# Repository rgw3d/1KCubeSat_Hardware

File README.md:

# 1KCubeSat_Hardware

Hardware design files for my $1000 cubesat.

Schematics & Layouts are done using KiCad V5.1+

## ½ CubeSat

My progress so far, what I'm calling the ½ Cubesat. The [avionics board](avionics_board) is stacked on the [eps board](eps_board)

## Radio Board

See [my fork of the OpenLST repo](https://github.com/rgw3d/openlst-hw/tree/1kcubesat-updates) for more information!

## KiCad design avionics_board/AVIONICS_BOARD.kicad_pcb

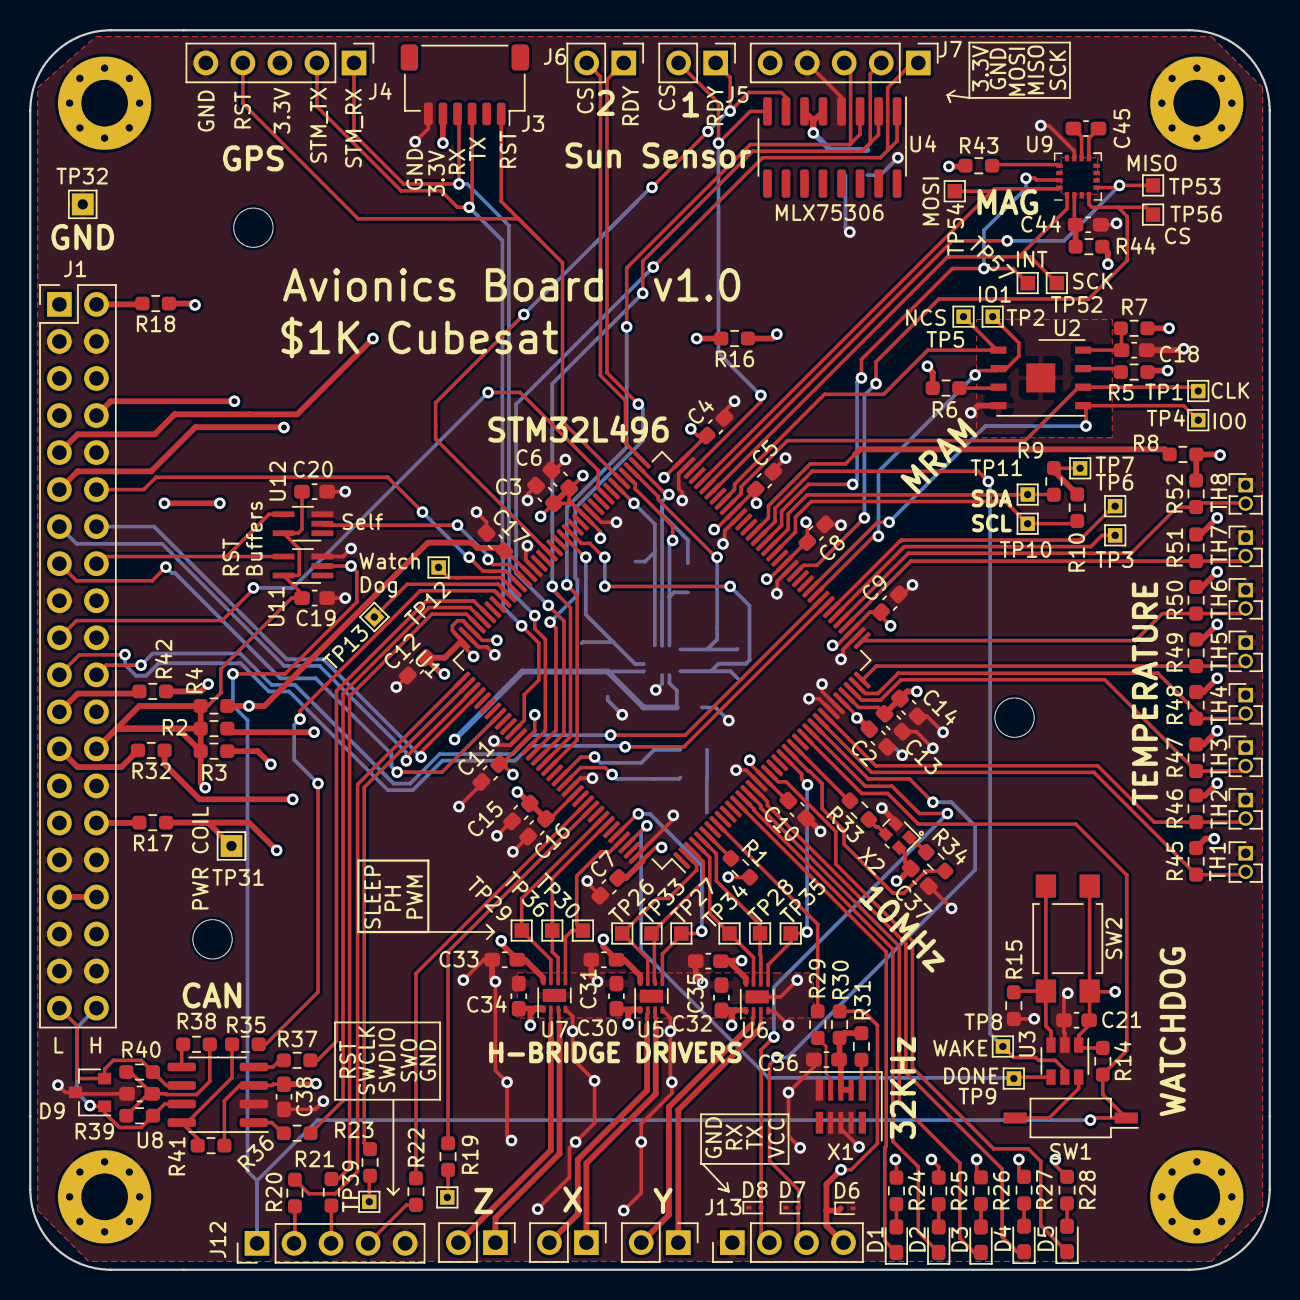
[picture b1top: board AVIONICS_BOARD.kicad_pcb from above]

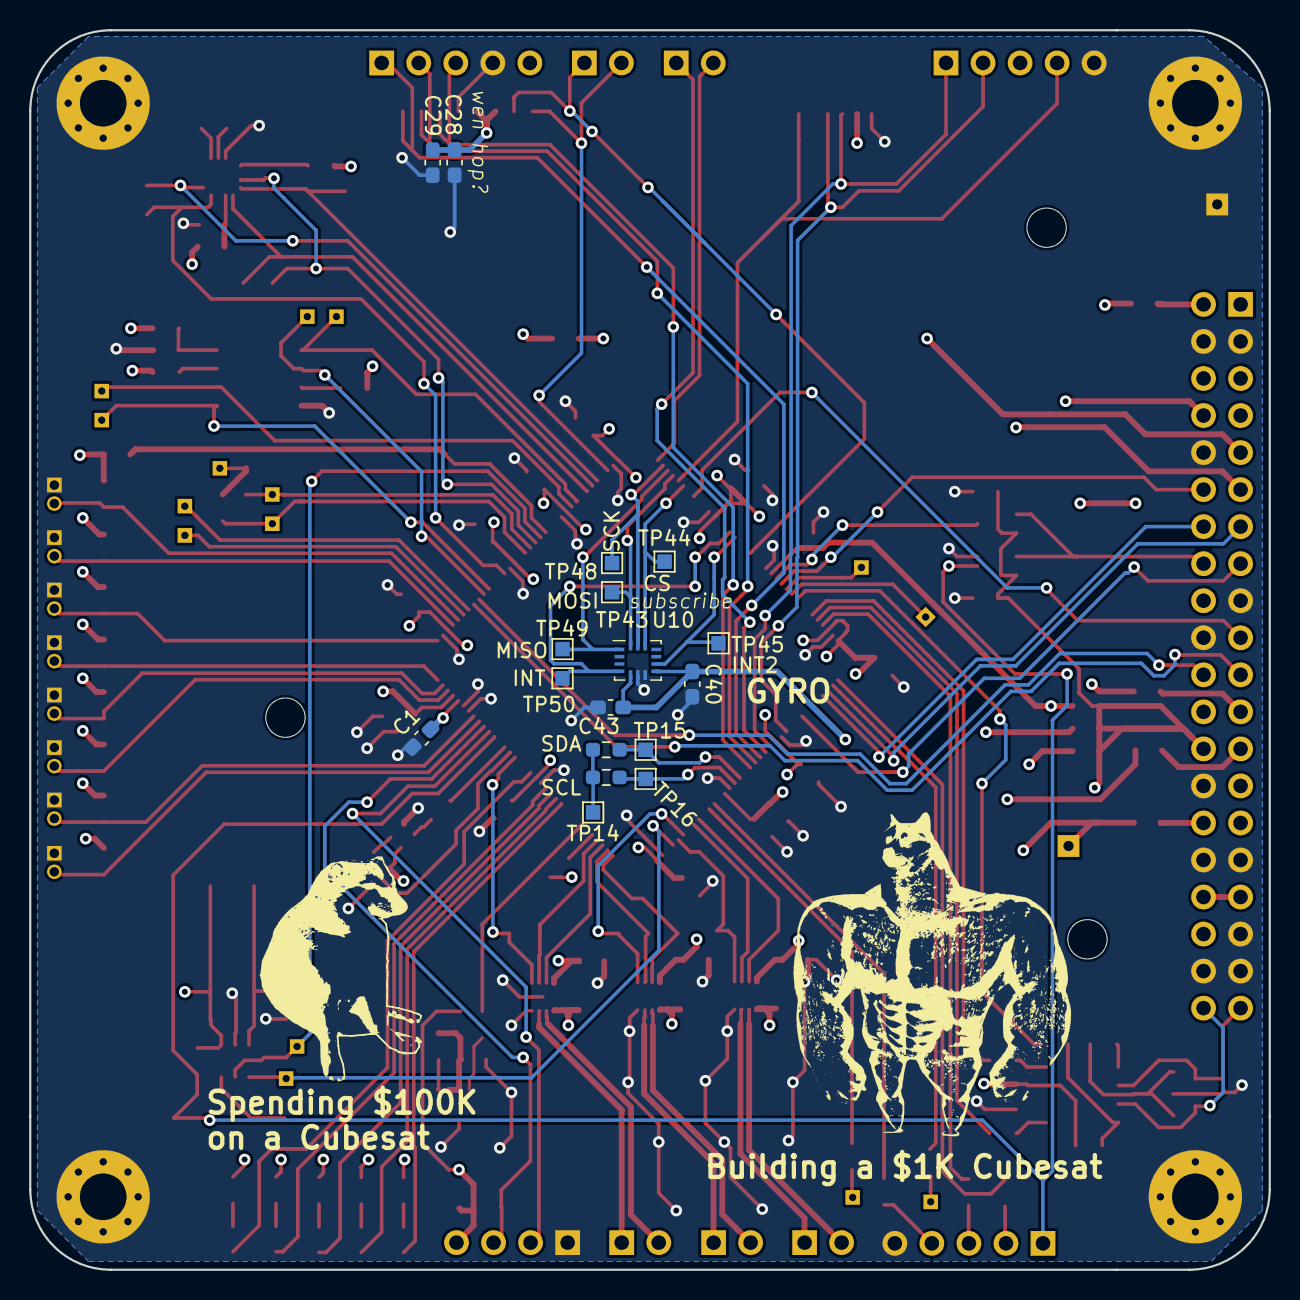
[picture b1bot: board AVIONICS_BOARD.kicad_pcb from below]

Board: 4 copper layers, 85.0 x 85.0 mm, 179 parts (17 on the bottom side), 143 nets.

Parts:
C1, C2, C13: 0.01uF; C_0603_1608Metric_Pad1.08x0.95mm_HandSolder
C3, C15: 4.7uF; C_0603_1608Metric_Pad1.08x0.95mm_HandSolder
C4, C5, C6, C7, C8, C9, C10, C11, C12, C16, C17, C18, C19, C20, C21, C29, C30, C31, C32, C33, C34, C35, C36, C37, C38, C40, C43: 0.1uF; C_0603_1608Metric_Pad1.08x0.95mm_HandSolder
C14, C28, C44: 1uF; C_0603_1608Metric_Pad1.08x0.95mm_HandSolder
C39: 4.7nF; C_0603_1608Metric_Pad1.08x0.95mm_HandSolder
C45: 10uF; C_0603_1608Metric_Pad1.08x0.95mm_HandSolder
D1: LED_SMD_RED; LED_0603_1608Metric_Pad1.05x0.95mm_HandSolder
D2: LED_SMD_GREEN; LED_0603_1608Metric_Pad1.05x0.95mm_HandSolder
D3, D4, D5: LED_SMD_YELLOW; LED_0603_1608Metric_Pad1.05x0.95mm_HandSolder
D6, D7, D8: ESD9B5.0ST5G; D_SOD-923
D9: NUP2105L; SOT-23
H1, H2, H3, H4: MountingHole_Pad; MountingHole_3.2mm_M3_Pad_Via
H5, H6, H7: MountingHole; MountingHole_2.7mm
J1: Conn_02x20_Odd_Even; PinHeader_2x20_P2.54mm_Vertical
J3: JST socket 6-pin 1mm pitch JST SH SM06B-SRSS-TB; JST_SH_SM06B-SRSS-TB_1x06-1MP_P1.00mm_Horizontal
J4, J7, J12: Conn_01x05; PinHeader_1x05_P2.54mm_Vertical
J5, J6, J9, J10, J11: Conn_01x02; PinHeader_1x02_P2.54mm_Vertical
J13: Conn_01x04_Male; PinHeader_1x04_P2.54mm_Vertical
R1, R8, R16, R17, R18, R29, R30, R31, R32, R33, R34, R35, R36, R37, R38, R42, R43, R44: 0; R_0603_1608Metric_Pad0.98x0.95mm_HandSolder
R2, R3, R4, R7: 10m; R_0603_1608Metric_Pad0.98x0.95mm_HandSolder
R5, R6, R14, R41: 100K; R_0603_1608Metric_Pad0.98x0.95mm_HandSolder
R9, R10, R11, R12: DNP; R_0603_1608Metric_Pad0.98x0.95mm_HandSolder
R15: 8.85K; R_0603_1608Metric_Pad0.98x0.95mm_HandSolder
R19, R20, R21, R22, R23: 49.9; R_0603_1608Metric_Pad0.98x0.95mm_HandSolder
R24, R25, R26, R27, R28: 330; R_0603_1608Metric_Pad0.98x0.95mm_HandSolder
R39, R40: 60.4; R_0603_1608Metric_Pad0.98x0.95mm_HandSolder
R45, R46, R47, R48, R49, R50, R51, R52: 47K; R_0603_1608Metric_Pad0.98x0.95mm_HandSolder
SW1: SW_DIP_x01; SW_DIP_SPSTx01_Slide_Copal_CHS-01B_W7.62mm_P1.27mm
SW2: SW_Push; SW_SPST_TL3305A
TH1, TH2, TH3, TH4, TH5, TH6, TH7, TH8: Thermistor_NTC; PinHeader_1x02_P1.27mm_Vertical
TP1, TP2, TP3, TP4, TP5, TP6, TP8, TP9: TP_smt_1x1; TestPoint_THTPad_1.0x1.0mm_Drill0.5mm
TP7, TP10, TP11, TP12, TP13: TP_tht_1x1; TestPoint_THTPad_1.0x1.0mm_Drill0.5mm
TP14, TP15, TP16, TP26, TP27, TP28, TP29, TP30, TP33, TP34, TP35, TP36, TP43, TP44, TP45, TP48, TP49, TP50, TP52, TP53, TP54, TP56, TP57: TP_smt_1x1; TestPoint_Pad_1.0x1.0mm
TP31, TP32: TP_1.5x1.5; TestPoint_THTPad_1.5x1.5mm_Drill0.7mm
TP37, TP39: TP_1.5x1.5; TestPoint_THTPad_1.0x1.0mm_Drill0.5mm
U1: STM32L496ZGTx; LQFP-144_20x20mm_P0.5mm
U2: MR25H10; DFN-8-1EP_6x5mm_P1.27mm_EP2x2mm
U3: TPL5010; SOT-23-6
U4: MLX75306; SOIC-16_3.9x9.9mm_P1.27mm
U5, U6, U7: DRV8838; WSON-8-1EP_2x2mm_P0.5mm_EP0.9x1.6mm
U8: SN65HVD230; SOIC-8_3.9x4.9mm_P1.27mm
U9: MMC5983MA; LGA-16_3x3mm_P0.5mm
U10: BMG250; Bosch_LGA-14_3x2.5mm_P0.5mm
U11, U12: 74LVC1G07; SOT-353_SC-70-5_Handsoldering
X1: TG-3541CE; Oscillator_SMD_SeikoEpson_TG3541CE-10Pin_3.2x2.5mm_HandSold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
X2: ECS-TXO-2016; Oscillator_SMD_ECS_TXO-2016-xx-xxx-4Pin_2.0x1.6mm

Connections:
/STM32L4/3.3V_ACS_LOGIC: J1.2, R18.2
/STM32L4/3.3V_CAN: C38.1, J1.5, R41.1, U8.3
/STM32L4/3.3V_CLK: J1.25, R32.2
/STM32L4/3.3V_GPS: J1.24, J3.5, J4.3
/STM32L4/3.3V_GYRO: J1.23, R42.2
/STM32L4/3.3V_MAG: J1.8, R43.2, R44.2
/STM32L4/3.3V_MRAM: J1.11, R5.1, R6.1, R7.2
/STM32L4/3.3V_SUN_SENSOR: J1.9, R16.2
/STM32L4/5V_ACS_COIL: J1.30, R17.2
/STM32L4/10MHZ_OE: R34.2, U1.22
/STM32L4/ACS/PWR_COIL: C30.1, C32.1, C34.1, R17.1, TP31.1, U5.1, U6.1, U7.1
/STM32L4/ACS/PWR_LOGIC: C31.1, C33.1, C35.1, R18.1, U5.8, U6.8, U7.8
/STM32L4/ACS_X_PH: TP33.1, U1.3, U5.6
/STM32L4/ACS_X_SLEEP: TP26.1, U1.2, U5.7
/STM32L4/ACS_Y_PH: TP28.1, U1.5, U6.6
/STM32L4/ACS_Y_SLEEP: TP34.1, U1.4, U6.7
/STM32L4/ACS_Z_PH: TP36.1, U1.137, U7.6
/STM32L4/ACS_Z_SLEEP: TP29.1, U1.136, U7.7
/STM32L4/ADC1_IN3: R45.1, TH1.2, U1.28
/STM32L4/ADC1_IN4: R46.1, TH2.2, U1.29
/STM32L4/ADC1_IN5: R47.1, TH3.2, U1.34
/STM32L4/ADC1_IN6: R48.1, TH4.2, U1.35
/STM32L4/ADC1_IN7: R49.1, TH5.2, U1.36
/STM32L4/ADC1_IN8: R50.1, TH6.2, U1.37
/STM32L4/ADC1_IN9: R51.1, TH7.2, U1.40
/STM32L4/ADC1_IN10: R52.1, TH8.2, U1.41
/STM32L4/ADC1_IN11: TP3.1, U1.42
/STM32L4/ADC1_IN12: TP6.1, U1.43
/STM32L4/AVI_RST: J1.16, U11.4, U12.4
/STM32L4/CAN1_RX: R37.2, U1.103
/STM32L4/CAN1_TX: R36.2, U1.104
/STM32L4/CAN_RS: R35.2, U1.100
/STM32L4/CAN_TRANSCEIVER/CANH: D9.1, J1.40, R39.1, U8.7
/STM32L4/CAN_TRANSCEIVER/CANL: D9.2, J1.39, R40.2, U8.6
/STM32L4/CAN_TRANSCEIVER/Vref: R38.2, U8.5
/STM32L4/EPS_RST: J1.12, U1.97
/STM32L4/GPS_RESET: J3.1, J4.4, U1.77
/STM32L4/GYRO_CS: TP44.1, U1.78, U10.12
/STM32L4/GYRO_INT_1: TP50.1, U1.87, U10.4
/STM32L4/GYRO_INT_2: TP45.1, U1.88, U10.9
/STM32L4/I2C1_SCL: R11.2, TP16.1, U1.129
/STM32L4/I2C1_SDA: R12.2, TP15.1, U1.128
/STM32L4/I2C4_SCL: R10.2, TP10.1, U1.54
/STM32L4/I2C4_SDA: R9.2, TP11.1, U1.55
/STM32L4/JTCK_SWCLK: R20.1, U1.109
/STM32L4/JTDI: R23.1, U1.110
/STM32L4/JTDO_TRACESWO: R22.1, U1.133
/STM32L4/JTMS_SWDIO: R21.1, U1.105
/STM32L4/LED_1: D1.1, U1.12
/STM32L4/LED_2: D2.1, U1.13
/STM32L4/LED_3: D3.1, U1.14
/STM32L4/LED_4: D4.1, U1.15
/STM32L4/LED_5: D5.1, U1.18
/STM32L4/LPUART1_RX: D8.2, J13.2, U1.26
/STM32L4/LPUART1_TX: D7.2, J13.3, U1.27
/STM32L4/MAG_CS: TP56.1, U1.50, U9.4
/STM32L4/MAG_INT: TP57.1, U1.56, U9.15
/STM32L4/MANUAL_RST: U1.96, U12.2
/STM32L4/NJRST: R19.1, U1.134
/STM32L4/OSC32_TCXO/OE: R31.1, X1.1
/STM32L4/QUADSPI_BK1_IO0: TP4.1, U1.47, U2.5
/STM32L4/QUADSPI_BK1_IO1: TP2.1, U1.46, U2.2
/STM32L4/QUADSPI_BK1_NCS: TP5.1, U1.64, U2.1
/STM32L4/QUADSPI_CLK: TP1.1, U1.63, U2.6
/STM32L4/RCC_OSC32_IN: R29.2, U1.8
/STM32L4/RCC_OSC_IN: R33.2, U1.23
/STM32L4/RST: J12.1, R14.2, SW1.1, U1.25, U11.2
/STM32L4/SPI1_MISO: TP53.1, U1.67, U9.5
/STM32L4/SPI1_MOSI: TP54.1, U1.68, U9.16
/STM32L4/SPI1_SCK: TP52.1, U1.66, U9.1
/STM32L4/SPI2_MISO: TP49.1, U1.75, U10.1
/STM32L4/SPI2_MOSI: TP43.1, U1.76, U10.14
/STM32L4/SPI2_SCK: TP48.1, U1.74, U10.13
/STM32L4/SPI3_MISO: J7.2, U1.125, U4.2
/STM32L4/SPI3_MOSI: J7.3, U1.126, U4.3
/STM32L4/SPI3_SCK: J7.1, U1.124, U4.1
/STM32L4/SUN_CS_1: J5.2, U1.70, U4.8
/STM32L4/SUN_CS_2: J6.2, U1.73
/STM32L4/SUN_FRAME_RDY_1: J5.1, U1.91, U4.7
/STM32L4/SUN_FRAME_RDY_2: J6.1, U1.123
/STM32L4/Sheet639EBCAF/5V0_2: J1.33, J1.34
/STM32L4/TEMPERATURE_ADC/INTRNL_VDD: R8.1, R45.2, R46.2, R47.2, R48.2, R49.2, R50.2, R51.2, R52.2
/STM32L4/TEMP_PWR: R8.2, U1.58
/STM32L4/TIM15_CH1: TP35.1, U1.21, U6.5
/STM32L4/TIM16_CH1: TP27.1, U1.139, U5.5
/STM32L4/TIM17_CH1: TP30.1, U1.140, U7.5
/STM32L4/UART4_RX: J1.14, U1.112
/STM32L4/UART4_TX: J1.13, U1.111
/STM32L4/USART2_RX: J3.4, J4.1, U1.122
/STM32L4/USART2_TX: J3.3, J4.2, U1.119
/STM32L4/USART3_CTS: J1.19, U1.80
/STM32L4/USART3_RTS: J1.15, U1.116
/STM32L4/USART3_RX: J1.22, U1.45
/STM32L4/USART3_TX: J1.21, U1.44
/STM32L4/WATCHDOG_DONE: TP9.1, U1.141, U3.4
/STM32L4/WATCHDOG_WAKE: TP8.1, U1.57, U3.5
GND: C1.1, C2.1, C3.1, C4.2, C5.2, C6.2, C7.2, C8.2, C9.2, C10.2, C11.1, C12.1, C13.2, C14.2, C15.1, C16.1, C17.1, C18.2, C19.1, C20.1, C21.2, C28.2, C29.2, C30.2, C31.2, C32.2, C33.2, C34.2, C35.2, C36.2, C37.2, C38.2, C39.2, C40.2, C43.2, C44.2, D6.2, D7.1, D8.1, D9.3, H1.1, H2.1, H3.1, H4.1, J1.3, J1.4, J1.10, J1.17, J1.20, J1.28, J1.31, J1.32, J1.35, J1.37, J1.38, J3.6, J4.5, J7.4, J12.5, J13.1, R15.2, TH1.1, TH2.1, TH3.1, TH4.1, TH5.1, TH6.1, TH7.1, TH8.1, TP32.1, U1.16, U1.30, U1.31, U1.38, U1.51, U1.61, U1.71, U1.83, U1.94, U1.107, U1.120, U1.130, U1.143, U2.4, U2.9, U3.2, U4.4, U5.4, U5.9, U6.4, U6.9, U7.4, U7.9, U8.2, U9.11, U10.6, U10.7, U11.3, U12.3, X1.5, X1.7, X1.8, X1.9, X2.2
unnamed: C1.2, C2.2, U1.32
unnamed: C3.2, C4.1, C5.1, C6.1, C7.1, C8.1, C9.1, C10.1, C11.2, C12.2, R1.2, R2.2, U1.17, U1.39, U1.52, U1.62, U1.72, U1.84, U1.106, U1.108, U1.121, U1.144
unnamed: C13.1, C14.1, R3.2, U1.33
unnamed: C15.2, C16.2, C17.2, R4.2, U1.95, U1.131
unnamed: C18.1, R7.1, U2.8
unnamed: C28.1, C29.1, J7.5, R16.1, U4.5, U4.6
unnamed: C36.1, R30.1, R31.2, X1.2, X1.3
unnamed: C37.1, R32.1, X2.4
unnamed: C39.1, R38.1, R39.2, R40.1
unnamed: C40.1, C43.1, R42.1, U10.5, U10.8
unnamed: C44.1, R44.1, U9.2
unnamed: C45.1, U9.9
unnamed: C45.2, U9.10
unnamed: D1.2, R24.2
unnamed: D2.2, R25.2
unnamed: D3.2, R26.2
unnamed: D4.2, R27.2
unnamed: D5.2, R28.2
unnamed: J9.1, U5.3
unnamed: J9.2, U5.2
unnamed: J10.1, U6.3
unnamed: J10.2, U6.2
unnamed: J11.1, U7.3
unnamed: J11.2, U7.2
unnamed: J12.2, R20.2
unnamed: J12.3, R21.2
unnamed: J12.4, R22.2
unnamed: R1.1, U1.6
unnamed: R5.2, U2.7
unnamed: R6.2, U2.3
unnamed: R9.1, R10.1, TP7.1
unnamed: R11.1, R12.1, TP14.1
unnamed: R15.1, SW2.2, U3.3
unnamed: R19.2, TP37.1
unnamed: R23.2, TP39.1
unnamed: R29.1, X1.4
unnamed: R33.1, X2.3
unnamed: R34.1, X2.1
unnamed: R35.1, R41.2, U8.8
unnamed: R36.1, U8.1
unnamed: R37.1, U8.4
unnamed: R43.1, U9.13
unnamed: SW1.2, U3.6
unnamed: TP12.1, U1.98
unnamed: TP13.1, U1.99
VCC: C19.2, C20.2, C21.1, D6.1, J1.26, J13.4, R2.1, R3.1, R4.1, R14.1, R24.1, R25.1, R26.1, R27.1, R28.1, R30.2, SW2.1, U3.1, U11.5, U12.5

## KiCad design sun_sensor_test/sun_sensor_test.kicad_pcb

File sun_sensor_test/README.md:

# Sun Sensor Test

Testing out a potential sun sensor using the K857PE 4-Quadrent Photodiode. See the [pdf](https://raw.githubusercontent.com/rgw3d/1KCubeSat_Hardware/master/sun_sensor_test/sun_sensor_test.pdf) for more information.

See [my video on this board](https://www.youtube.com/watch?v=8ttuiI6RIH0) for more information.

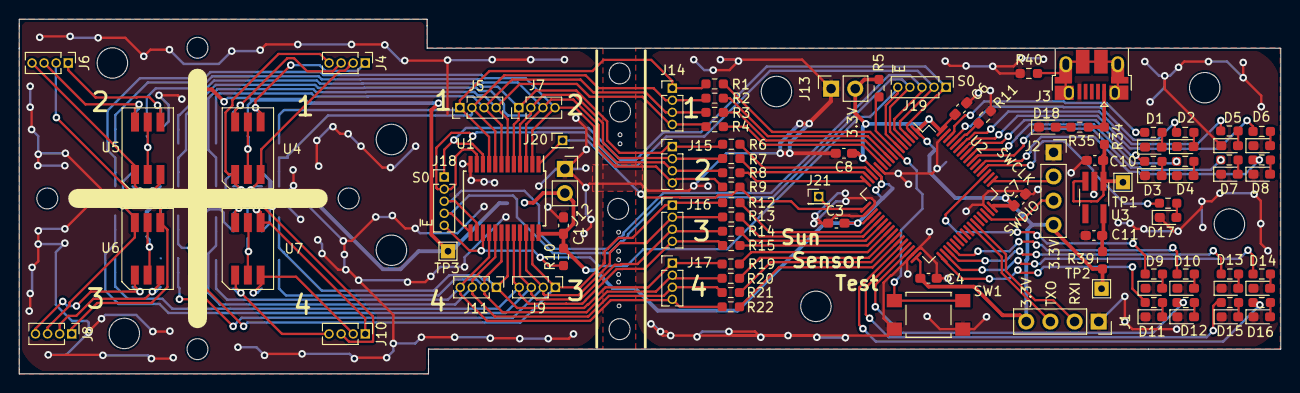
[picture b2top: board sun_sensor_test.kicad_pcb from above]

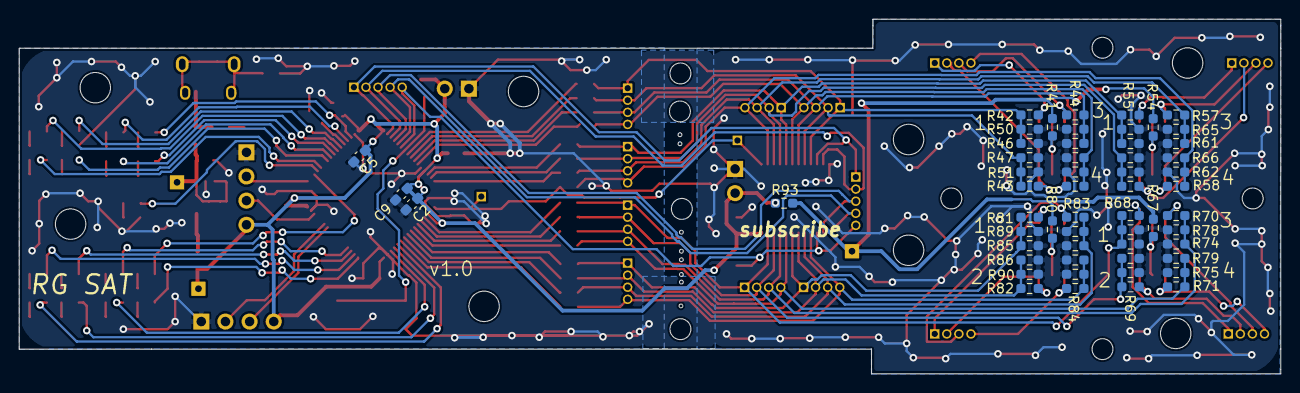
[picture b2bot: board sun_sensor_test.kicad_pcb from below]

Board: 2 copper layers, 132.7 x 37.3 mm, 178 parts (56 on the bottom side), 105 nets.

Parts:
C1, C2, C3, C4, C5, C6, C7: 0.1uF; C_0603_1608Metric_Pad1.08x0.95mm_HandSolder
C8, C9: 1uF; C_0603_1608Metric_Pad1.08x0.95mm_HandSolder
C10, C11: 4.7uF; C_0603_1608Metric_Pad1.08x0.95mm_HandSolder
D1, D2, D3, D4, D5, D6, D7, D8, D9, D10, D11, D12, D13, D14, D15, D16, D17, D18: RED; LED_0603_1608Metric_Pad1.05x0.95mm_HandSolder
H1, H2, H3, H4, H5, H6, H7, H8: M2 Screw; MountingHole_2.2mm_M2_ISO7380
H9, H10, H11, H12, H13, H14, H15, H16: M3 Screw; MountingHole_3.2mm_M3
H17, H18, H19, H20, H21, H23, H24, H25: mousebite
J1, J2: 2.54mm; PinSocket_1x04_P2.54mm_Vertical
J3: USB_B_Micro; USB_Micro-B_Amphenol_10103594-0001LF_Horizontal
J4, J5, J6, J7, J8, J9, J10, J11, J14, J15, J16, J17: Conn_01x04_Female; PinHeader_1x04_P1.27mm_Vertical
J12, J13: Conn_01x02; PinSocket_1x02_P2.54mm_Vertical
J18, J19: Conn_01x05_Female; PinHeader_1x05_P1.27mm_Vertical
J20, J21: 1.27mm; PinHeader_1x01_P1.27mm_Vertical
R1, R2, R3, R4, R6, R7, R8, R9, R12, R13, R14, R15, R19, R20, R21, R22, R40, R46, R47, R48, R49, R50, R51, R52, R53, R59, R60, R61, R62, R63, R64, R65, R66, R72, R73, R74, R75, R76, R77, R78, R79, R85, R86, R87, R88, R89, R90, R91, R92: DNP; R_0603_1608Metric_Pad0.98x0.95mm_HandSolder
R5, R11: 10K; R_0603_1608Metric_Pad0.98x0.95mm_HandSolder
R10: 100K; R_0603_1608Metric_Pad0.98x0.95mm_HandSolder
R16, R17, R18, R23, R24, R25, R26, R27, R28, R29, R30, R31, R32, R33, R36, R37, R38: 680; R_0603_1608Metric_Pad0.98x0.95mm_HandSolder
R34, R39, R41, R42, R43, R44, R45, R54, R55, R56, R57, R58, R67, R68, R69, R70, R71, R80, R81, R82, R83, R84, R93: 0; R_0603_1608Metric_Pad0.98x0.95mm_HandSolder
R35: 330; R_0603_1608Metric_Pad0.98x0.95mm_HandSolder
SW1: SW_Push; SW_SPST_TL3305A
TP1, TP2, TP3: TP_1.5x1.5; TestPoint_THTPad_1.5x1.5mm_Drill0.7mm
U1: CD74HC4067SM; SSOP-24_5.3x8.2mm_P0.65mm
U2: STM32L051R8Tx; LQFP-64_10x10mm_P0.5mm
U3: ADP150AUJZ-3.3-R7; TSOT-23-5_HandSoldering
U4, U5, U6, U7: K857PE

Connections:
+3V3: C1.1, C2.1, C3.1, C4.1, C5.1, C6.1, C7.1, C8.1, C9.1, J1.4, J2.4, J12.2, J13.2, R5.2, R10.2, R39.2, R93.2, TP2.1, U1.24, U2.1, U2.13, U2.19, U2.32, U2.48, U2.64
+5V: C10.1, R34.2, TP1.1, U3.1, U3.3
/AIN0: R1.1, U2.8
/AIN1: R2.1, U2.9
/AIN2: R3.1, U2.10
/AIN3: R4.1, U2.11
/AIN4: R6.1, U2.14
/AIN5: R7.1, U2.15
/AIN6: R8.1, U2.16
/AIN7: J20.1, J21.1, R9.1, U1.1, U2.17
/AIN8: R12.1, U2.20
/AIN9: R13.1, U2.21
/AIN10: R14.1, U2.22
/AIN11: R15.1, U2.23
/AIN12: R19.1, U2.24
/AIN13: R20.1, U2.25
/AIN14: R21.1, U2.26
/AIN15: R22.1, U2.27
/D1: R16.1, U2.62
/D2: R17.1, U2.61
/D3: R18.1, U2.57
/D4: R23.1, U2.56
/D5: R24.1, U2.59
/D6: R25.1, U2.58
/D7: R26.1, U2.55
/D8: R27.1, U2.53
/D9: R28.1, U2.51
/D10: R29.1, U2.36
/D11: R30.1, U2.33
/D12: R31.1, U2.30
/D13: R32.1, U2.35
/D14: R33.1, U2.34
/D15: R36.1, U2.29
/D16: R37.1, U2.28
/D17: R38.1, U2.52
/K857PE Breakout/A1: J5.1, J14.1, R1.2, R42.1, R46.2, R50.2, U1.9
/K857PE Breakout/A2: J5.2, J14.2, R2.2, R43.1, R47.2, R51.2, U1.8
/K857PE Breakout/A3: J5.3, J14.3, R3.2, R44.1, R48.2, R52.2, U1.7
/K857PE Breakout/A4: J5.4, J14.4, R4.2, R45.1, R49.2, R53.2, U1.6
/K857PE Breakout/VBIAS: R41.1, R54.1, R67.1, R80.1, R93.1, TP3.1
/S0: J18.1, J19.1, U1.10, U2.2
/S1: J18.2, J19.2, U1.11, U2.3
/S2: J18.3, J19.3, U1.14, U2.4
/S3: J18.4, J19.4, U1.13, U2.5
/SWCLK: J2.2, U2.49
/SWDIO: J2.3, U2.46
/USART1_RX: J1.2, U2.43
/USART1_TX: J1.3, U2.42
/sheet60017AC6/A1: J7.1, J15.1, R6.2, R55.1, R59.2, R63.2, U1.5
/sheet60017AC6/A2: J7.2, J15.2, R7.2, R56.1, R60.2, R64.2, U1.4
/sheet60017AC6/A3: J7.3, J15.3, R8.2, R57.1, R61.2, R65.2, U1.3
/sheet60017AC6/A4: J7.4, J15.4, R9.2, R58.1, R62.2, R66.2, U1.2
/sheet60017C33/A1: J9.1, J16.1, R12.2, R68.1, R72.2, R76.2, U1.23
/sheet60017C33/A2: J9.2, J16.2, R13.2, R69.1, R73.2, R77.2, U1.22
/sheet60017C33/A3: J9.3, J16.3, R14.2, R70.1, R74.2, R78.2, U1.21
/sheet60017C33/A4: J9.4, J16.4, R15.2, R71.1, R75.2, R79.2, U1.20
/sheet60017CBC/A1: J11.1, J17.1, R19.2, R81.1, R85.2, R89.2, U1.19
/sheet60017CBC/A2: J11.2, J17.2, R20.2, R82.1, R86.2, R90.2, U1.18
/sheet60017CBC/A3: J11.3, J17.3, R21.2, R83.1, R87.2, R91.2, U1.17
/sheet60017CBC/A4: J11.4, J17.4, R22.2, R84.1, R88.2, R92.2, U1.16
/~E: J18.5, J19.5, R10.1, U1.15, U2.6
GND: C1.2, C2.2, C3.2, C4.2, C5.2, C6.2, C7.2, C8.2, C9.2, C10.2, C11.2, D1.1, D2.1, D3.1, D4.1, D5.1, D6.1, D7.1, D8.1, D9.1, D10.1, D11.1, D12.1, D13.1, D14.1, D15.1, D16.1, D17.1, D18.1, J1.1, J2.1, J3.5, J12.1, J13.1, R11.1, R40.1, R46.1, R47.1, R48.1, R49.1, R50.1, R51.1, R52.1, R53.1, R59.1, R60.1, R61.1, R62.1, R63.1, R64.1, R65.1, R66.1, R72.1, R73.1, R74.1, R75.1, R76.1, R77.1, R78.1, R79.1, R85.1, R86.1, R87.1, R88.1, R89.1, R90.1, R91.1, R92.1, SW1.1, U1.12, U2.12, U2.18, U2.31, U2.47, U2.63, U3.2
unnamed: C11.1, R39.1, U3.5
unnamed: D1.2, R16.2
unnamed: D2.2, R17.2
unnamed: D3.2, R18.2
unnamed: D4.2, R23.2
unnamed: D5.2, R24.2
unnamed: D6.2, R25.2
unnamed: D7.2, R26.2
unnamed: D8.2, R27.2
unnamed: D9.2, R28.2
unnamed: D10.2, R29.2
unnamed: D11.2, R30.2
unnamed: D12.2, R31.2
unnamed: D13.2, R32.2
unnamed: D14.2, R33.2
unnamed: D15.2, R36.2
unnamed: D16.2, R37.2
unnamed: D17.2, R38.2
unnamed: D18.2, R35.2
unnamed: J3.1, R34.1, R35.1
unnamed: J3.6, R40.2
unnamed: J4.1, R42.2, U4.4
unnamed: J4.2, R43.2, U4.3
unnamed: J4.3, R44.2, U4.6
unnamed: J4.4, R45.2, U4.1
unnamed: J6.1, R55.2, U5.4
unnamed: J6.2, R56.2, U5.3
unnamed: J6.3, R57.2, U5.6
unnamed: J6.4, R58.2, U5.1
unnamed: J8.1, R68.2, U6.4
unnamed: J8.2, R69.2, U6.3
unnamed: J8.3, R70.2, U6.6
unnamed: J8.4, R71.2, U6.1
unnamed: J10.1, R81.2, U7.4
unnamed: J10.2, R82.2, U7.3
unnamed: J10.3, R83.2, U7.6
unnamed: J10.4, R84.2, U7.1
unnamed: R5.1, SW1.2, U2.7
unnamed: R11.2, U2.60
unnamed: R41.2, U4.2, U4.5
unnamed: R54.2, U5.2, U5.5
unnamed: R67.2, U6.2, U6.5
unnamed: R80.2, U7.2, U7.5
